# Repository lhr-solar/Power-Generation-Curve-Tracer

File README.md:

# :sunny: PV Curve Tracer

- [:sunny: PV Curve Tracer](#sunny-pv-curve-tracer)
  - [Repository Structure](#repository-structure)
  - [Maintainers and Contribution](#maintainers-and-contribution)
  - [Versioning](#versioning)
  - [TODO](#todo)

---

## Repository Structure

- **datasheets** - contains datasheets for major components of the PV Curve Tracer.
- **docs** - contains documentation on how to build, test, and use the PV Curve Tracer.
- **fw** - contains fw that is loaded onto the PV Curve Tracer.
  - **tests** - test programs used to characterize and validate the PV Curve Tracer.
  - **src** - main program used to run the PV Curve Tracer.
  - **inc** - internally developed libraries specific for the PV Curve Tracer.
  - **lib** - third party libraries used by the PV Curve Tracer.
- **hw**
  - **Footprints** - project specfic footprint association files for the PV Curve Tracer.
  - **Models** - 3d .step files for the PCB 3d viewer.
  - **Symbols** - project specific symbol files for the PV Curve Tracer.
  - **vX_Y_Z** - frozen versioning folder for PCB production files.

---

## Maintainers and Contribution

The current maintainer of this project is Matthew Yu as of 05/20/2023. His email
is [matthewjkyu@gmail.com](matthewjkyu@gmail.com).

Contributors to the HW and FW encompass many dedicated students, including:

- Roy Mor
- Afnan Mir
- Youssef Elsherif

Special thanks to Professor Gary Hallock, who supervised the development and
design of this project.

---

## Versioning

This PCB is on unified version `1.3.0`. Every time the schematic and/or layout
is updated, this version number should go up. We use [semantic
versioning](https://semver.org/) to denote between versions. See the
[changelog](./docs/CHANGELOG.md) for more details.

---

## TODO

Documentation

- Update assembly and testing document, ordering document, and improvement document.
- Add datasheets for key components of the device.

HW

- check if v1.2.0 bodges has been fixed (op amps, regulator)
   Complete v1.4.0rc board candidate

SW

- Regenerate code for MBED with proposed filestructure

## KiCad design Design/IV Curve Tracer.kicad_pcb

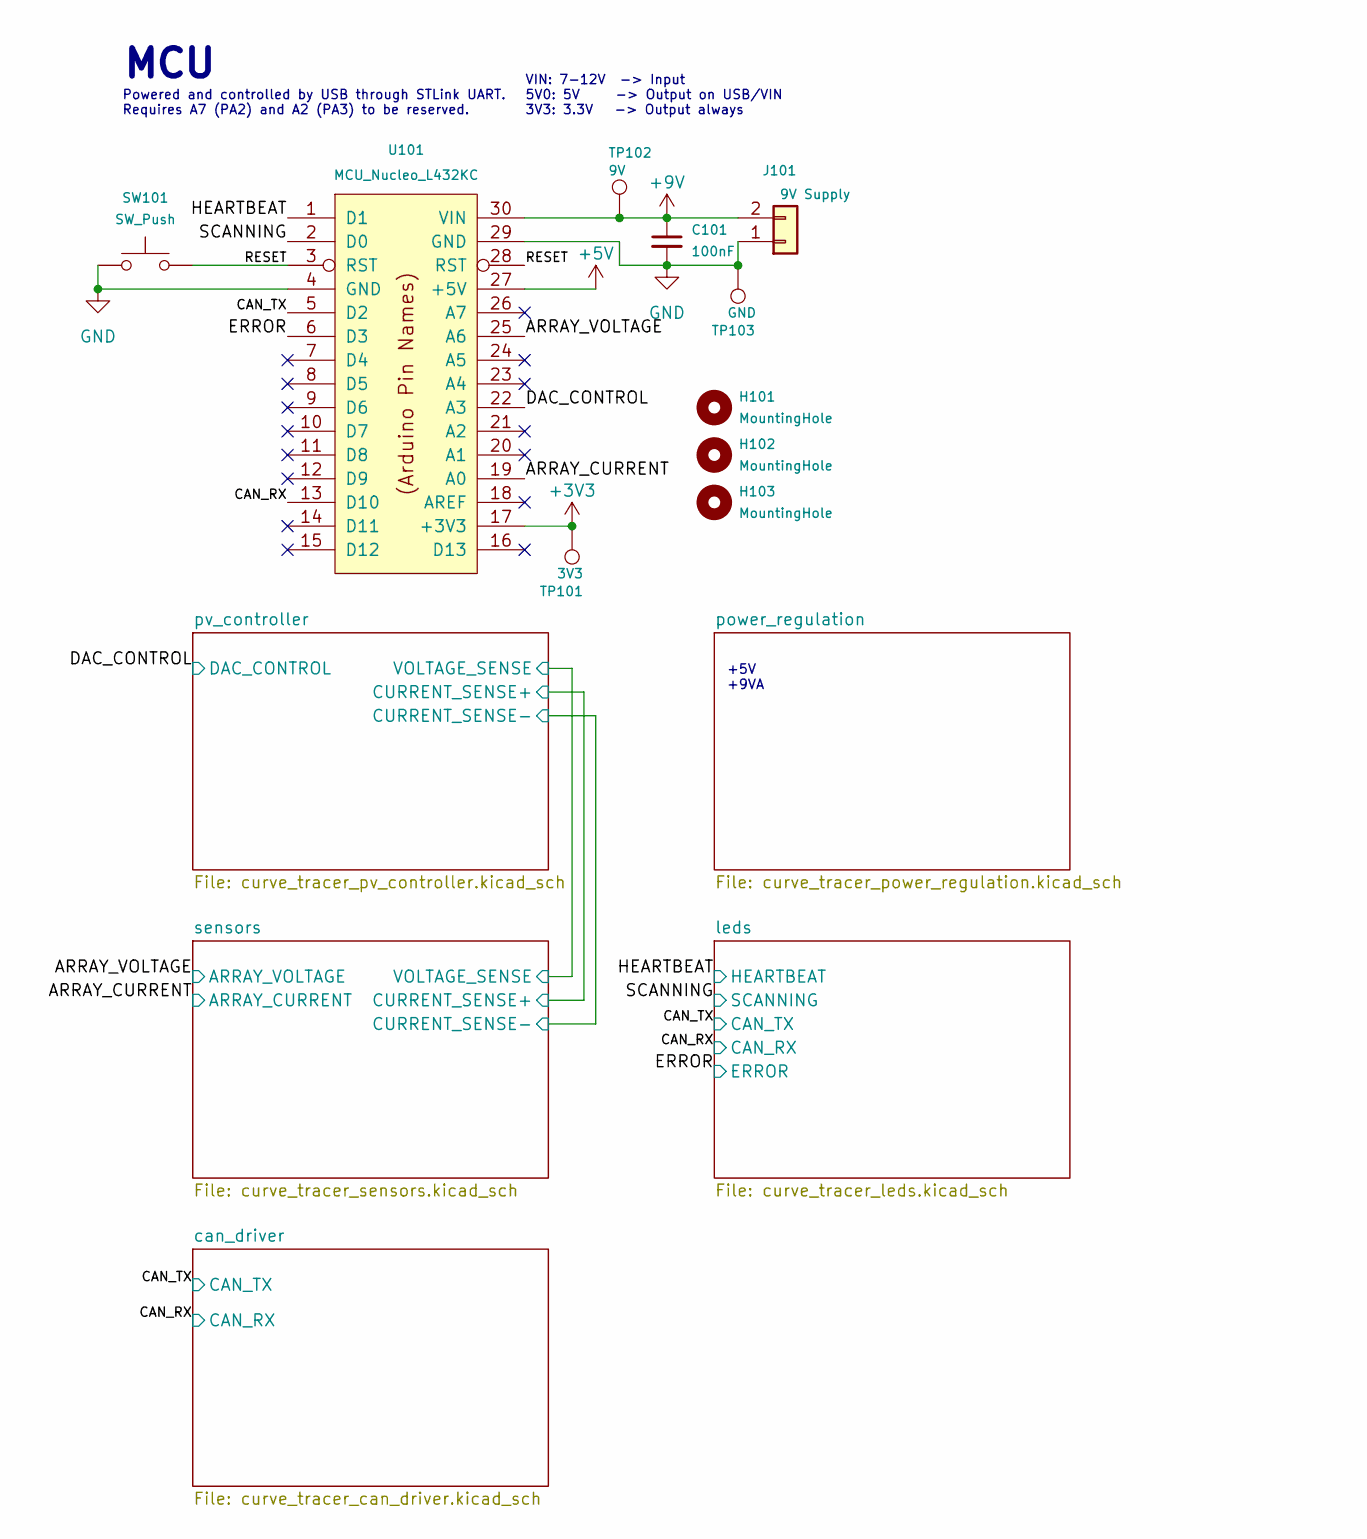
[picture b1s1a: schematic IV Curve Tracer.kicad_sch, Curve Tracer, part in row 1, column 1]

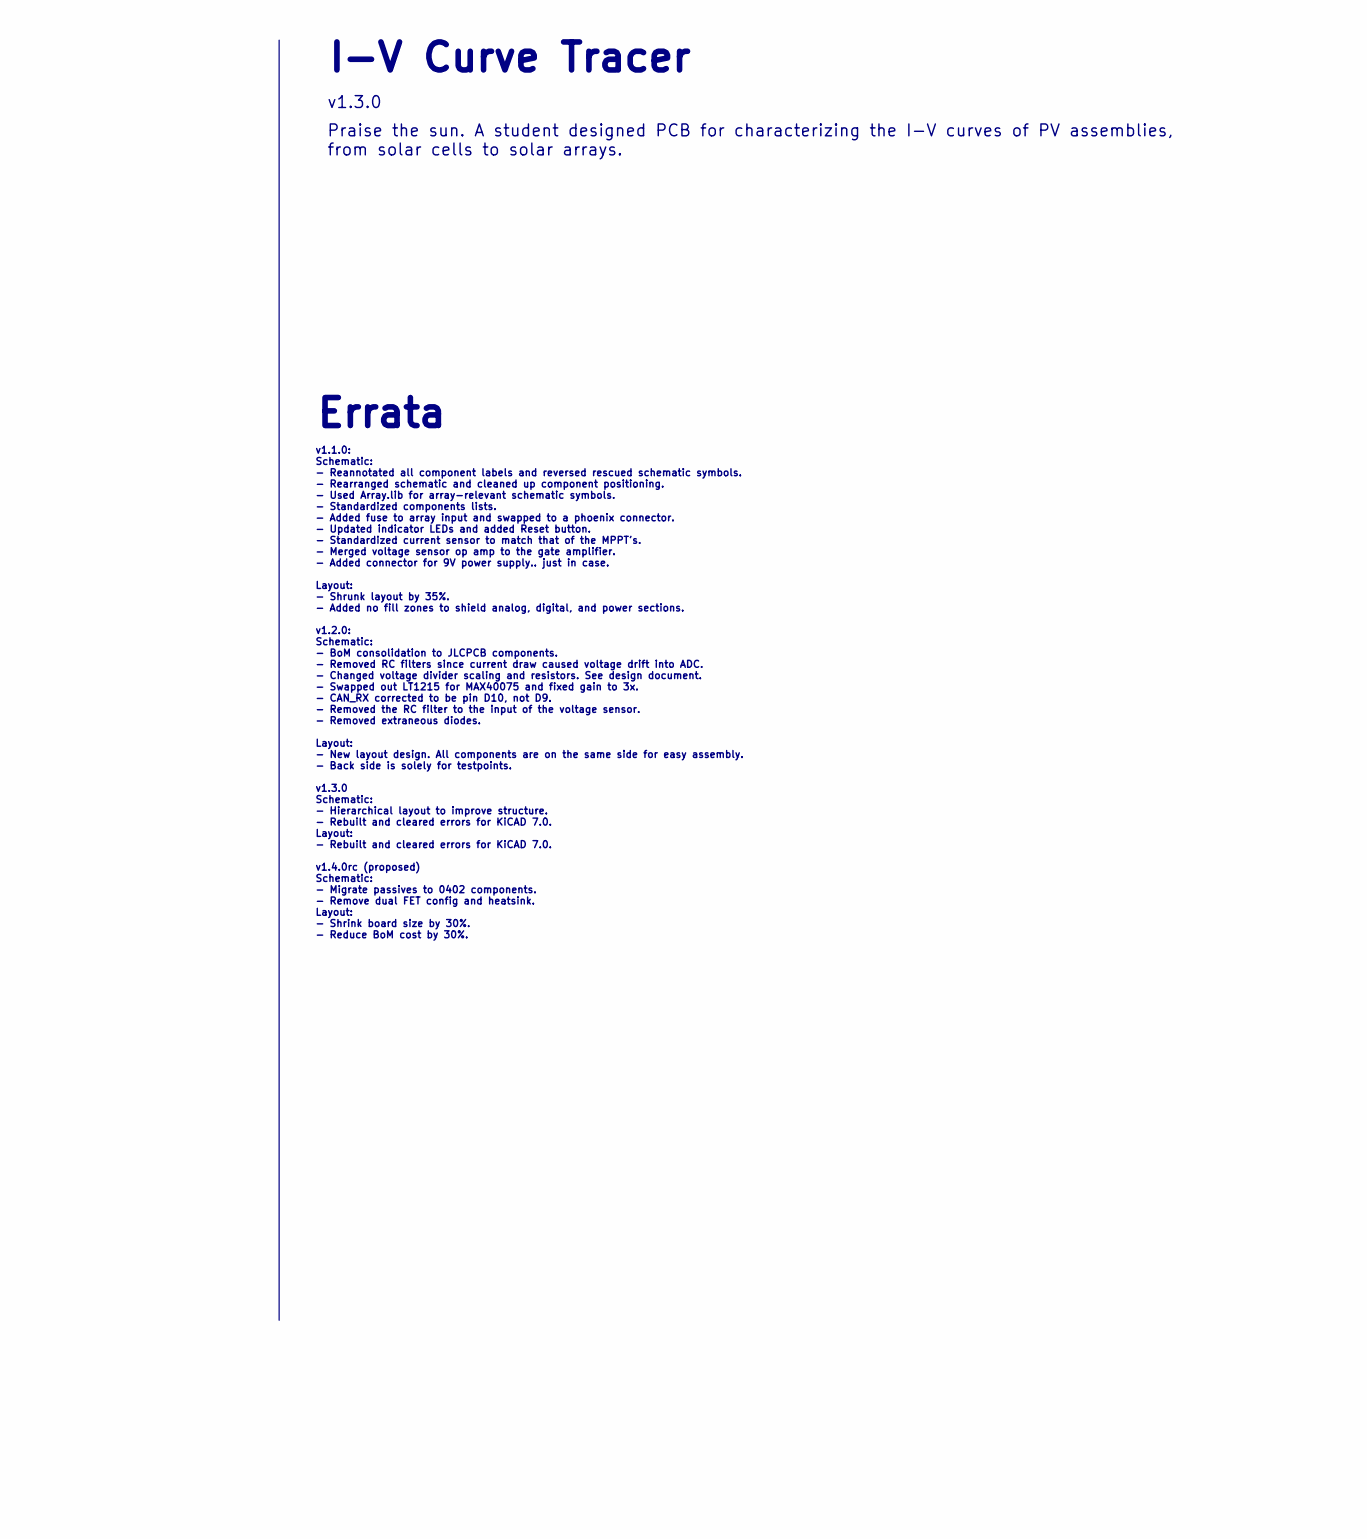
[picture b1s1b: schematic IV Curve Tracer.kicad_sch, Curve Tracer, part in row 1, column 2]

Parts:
C101: 100nF; C_0805_2012Metric; LCSC Part # C28233
H101, H102, H103: MountingHole; MountingHole_2.2mm_M2
J101: 9V Supply; Molex_Micro-Fit_3.0_43650-0215_1x02_P3.00mm_Vertical
SW101: SW_Push; SW_PUSH_6mm
TP101: 3V3; TestPoint_Pad_1.0x1.0mm
TP102: 9V; TestPoint_Pad_1.0x1.0mm
TP103: GND; TestPoint_Pad_1.0x1.0mm
U101: MCU_Nucleo_L432KC; MODULE_NUCLEO-L432KC

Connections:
+3V3: TP101.1, U101.17 (+3V3); also elsewhere on the board
+5V: U101.27 (+5V); also elsewhere on the board
+9V: C101.1, J101.2, TP102.1, U101.30 (VIN)
/ARRAY_CURRENT: U101.19 (A0); also elsewhere on the board
/ARRAY_VOLTAGE: U101.25 (A6); also elsewhere on the board
/CAN_RX: U101.13 (D10); also elsewhere on the board
/CAN_TX: U101.5 (D2); also elsewhere on the board
/DAC_CONTROL: U101.22 (A3); also elsewhere on the board
/ERROR: U101.6 (D3); also elsewhere on the board
/HEARTBEAT: U101.1 (D1); also elsewhere on the board
/RESET: SW101.2, U101.3 (RST), U101.28 (RST)
/SCANNING: U101.2 (D0); also elsewhere on the board
GND: C101.2, J101.1, SW101.1, TP103.1, U101.4 (GND), U101.29 (GND); also elsewhere on the board

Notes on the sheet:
Errata
Praise the sun. A student designed PCB for characterizing the I-V curves of PV assemblies, from solar cells to solar arrays.
I-V Curve Tracer
+5V +9VA
MCU
Powered and controlled by USB through STLink UART. Requires A7 (PA2) and A2 (PA3) to be reserved.
v1.1.0: Schematic: - Reannotated all component labels and reversed rescued schematic symbols. - Rearranged schematic and cleaned up component positioning. - Used Array.lib for array-relevant schematic symbols. - Standardized components lists. - Added fuse to array input and swapped to a phoenix con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
v1.3.0
VIN: 7-12V -> Input 5V0: 5V -> Output on USB/VIN 3V3: 3.3V -> Output always

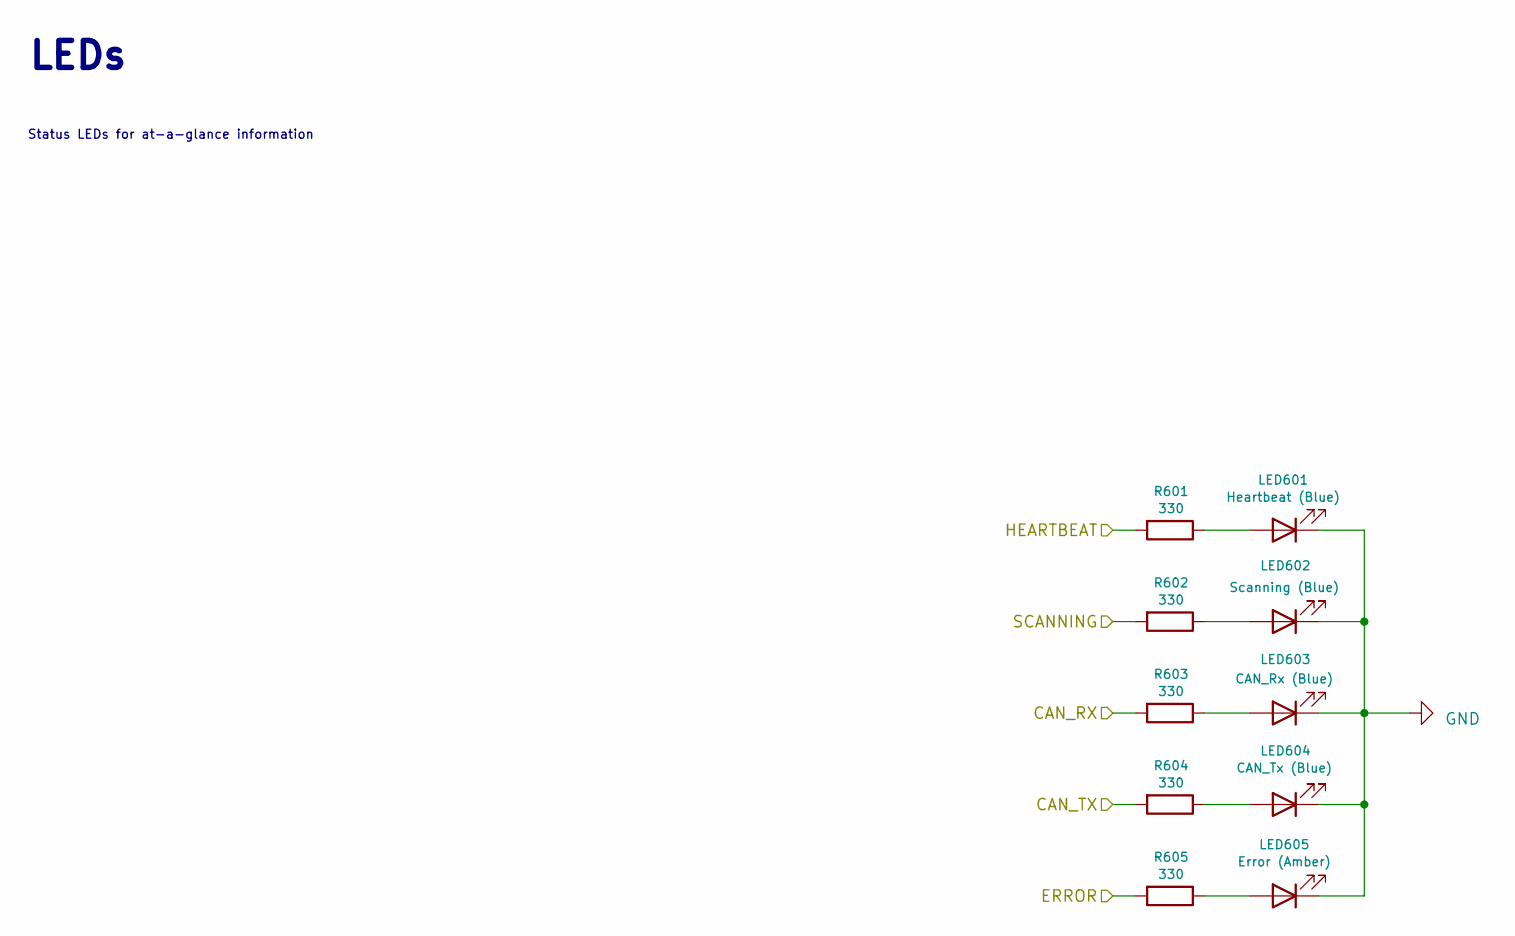
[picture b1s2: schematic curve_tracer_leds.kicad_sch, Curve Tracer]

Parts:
LED601: Heartbeat (Blue); LED_0805_2012Metric
LED602: Scanning (Blue); LED_0805_2012Metric
LED603: CAN_Rx (Blue); LED_0805_2012Metric
LED604: CAN_Tx (Blue); LED_0805_2012Metric
LED605: Error (Amber); LED_0805_2012Metric
R601, R602, R603, R604, R605: 330; R_0805_2012Metric; LCSC Part # C17630

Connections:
/CAN_RX: R603.2; also elsewhere on the board
/CAN_TX: R604.2; also elsewhere on the board
/ERROR: R605.2; also elsewhere on the board
/HEARTBEAT: R601.2; also elsewhere on the board
/SCANNING: R602.2; also elsewhere on the board
GND: LED601.1 (K), LED602.1 (K), LED603.1 (K), LED604.1 (K), LED605.1 (K); also elsewhere on the board
unnamed: LED601.2 (A), R601.1
unnamed: LED602.2 (A), R602.1
unnamed: LED603.2 (A), R603.1
unnamed: LED604.2 (A), R604.1
unnamed: LED605.2 (A), R605.1

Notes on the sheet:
Status LEDs for at-a-glance information
LEDs

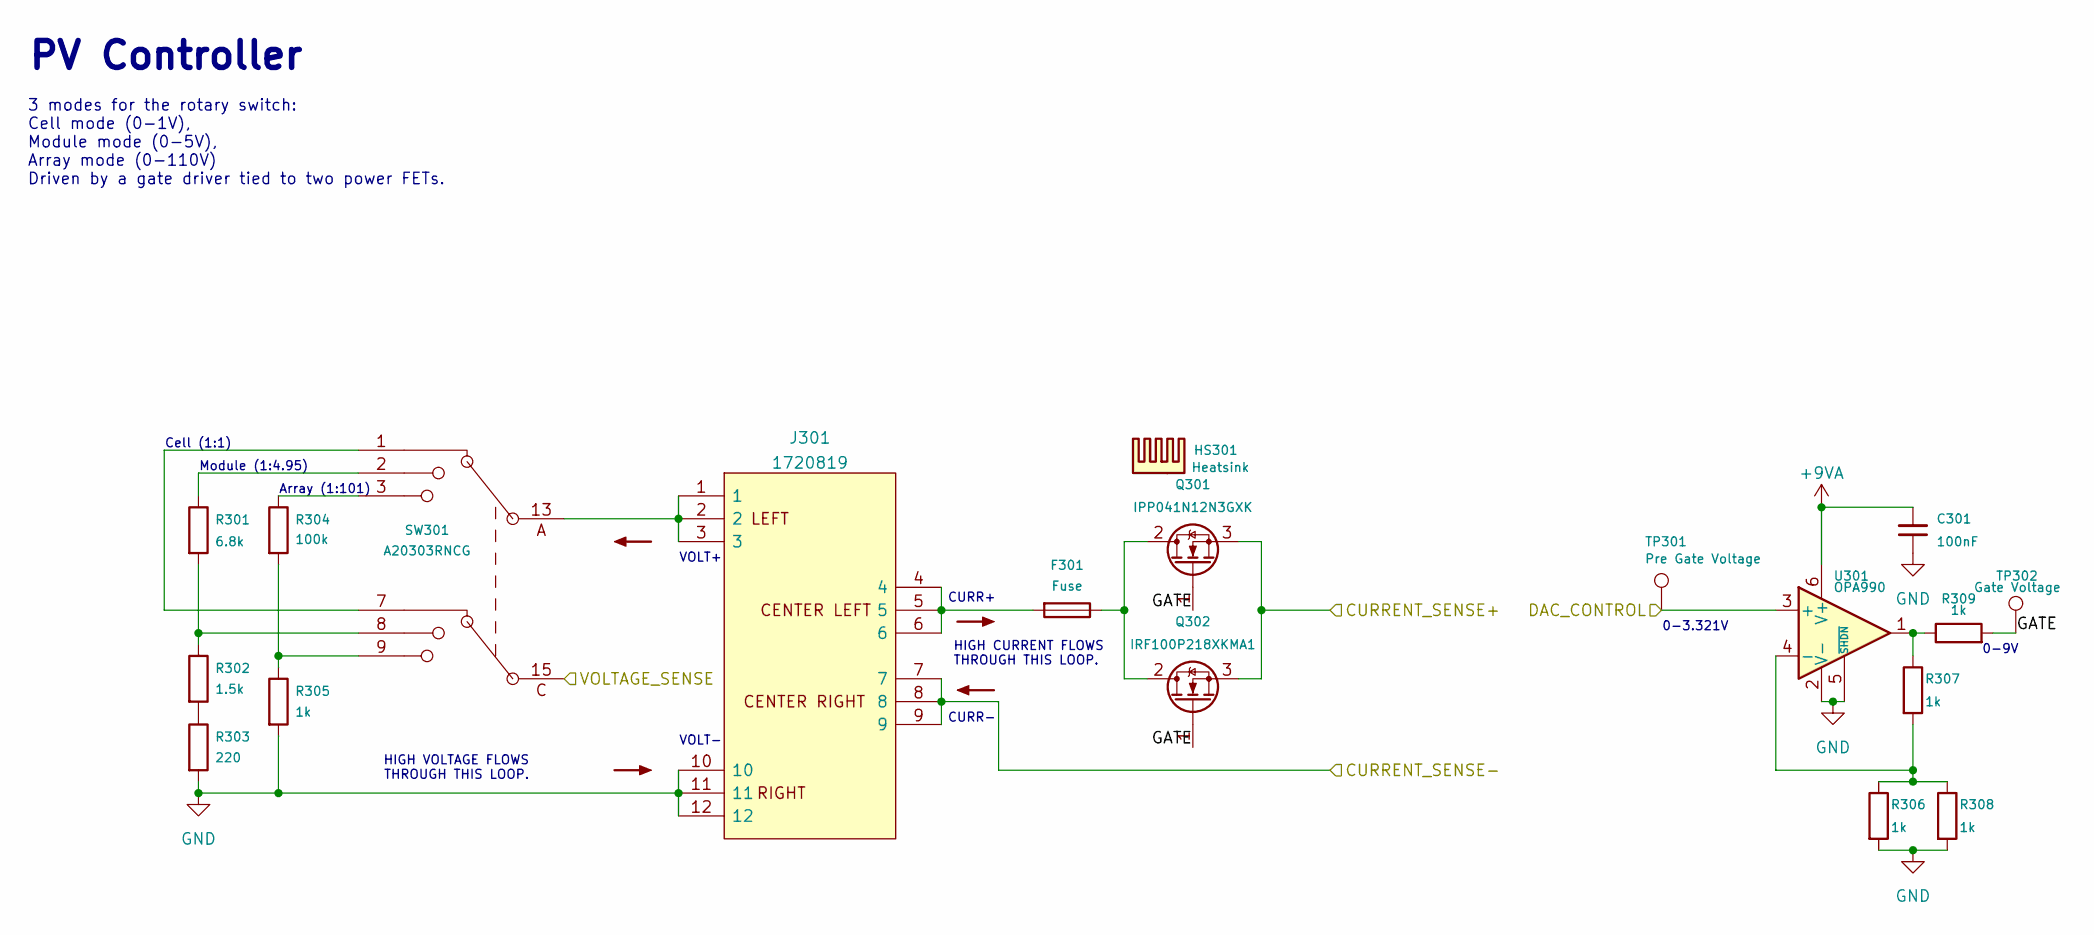
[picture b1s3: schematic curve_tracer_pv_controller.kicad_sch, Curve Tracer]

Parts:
C301: 100nF; C_0805_2012Metric; LCSC Part # C28233
F301: Fuse; 05200101Z_Fuze_Holder_5x20_PCB_Mount
HS301: Heatsink; Heatsink_Fischer_SK129-STS_42x25mm_2xDrill2.5mm
J301: 1720819
Q301: IPP041N12N3GXK; TO-220-3_Vertical
Q302: IRF100P218XKMA1; TO-220-3_Vertical
R301: 6.8k; R_0805_2012Metric; LCSC Part # C17772
R302: 1.5k; R_0805_2012Metric; LCSC Part # C4310
R303: 220; R_0805_2012Metric; LCSC Part # C17557
R304: 100k; R_0805_2012Metric; LCSC Part # C149504
R305, R306, R307, R308, R309: 1k; R_0805_2012Metric; LCSC Part # C17513
SW301: A20303RNCG; A20303RNCG_rotary_sw_dp3t
TP301: Pre Gate Voltage; TestPoint_Pad_1.0x1.0mm
TP302: Gate Voltage; TestPoint_Pad_1.0x1.0mm
U301: OPA990; SOT-23-6

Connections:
+9VA: C301.2, U301.6 (V+); also elsewhere on the board
/DAC_CONTROL: TP301.1, U301.3 (+); also elsewhere on the board
/pv_controller/CURRENT_SENSE+: Q301.3 (S), Q302.3 (S); also elsewhere on the board
/pv_controller/CURRENT_SENSE-: J301.7, J301.8, J301.9; also elsewhere on the board
/pv_controller/GATE: Q301.1 (G), Q302.1 (G), R309.2, TP302.1
/pv_controller/VOLTAGE_SENSE: SW301.15 (C); also elsewhere on the board
GND: C301.1, J301.10, J301.11, J301.12, R303.2, R305.2, R306.2, R308.2, U301.2 (V-), U301.5 (~SHDN); also elsewhere on the board
unnamed: F301.2, J301.4, J301.5, J301.6
unnamed: F301.1, Q301.2 (D), Q302.2 (D)
unnamed: R301.1, SW301.2
unnamed: R301.2, R302.1, SW301.8
unnamed: R302.2, R303.1
unnamed: R304.1, SW301.3
unnamed: R304.2, R305.1, SW301.9
unnamed: R307.1, R309.1, U301.1
unnamed: J301.1, J301.2, J301.3, SW301.13 (A)
unnamed: SW301.1, SW301.7
unnamed: R306.1, R307.2, R308.1, U301.4 (-)

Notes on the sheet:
PV Controller
VOLT+
0-3.321V
HIGH CURRENT FLOWS THROUGH THIS LOOP.
3 modes for the rotary switch: Cell mode (0-1V), Module mode (0-5V), Array mode (0-110V) Driven by a gate driver tied to two power FETs.
CURR+
Module (1:4.95)
0-9V
CURR-
HIGH VOLTAGE FLOWS THROUGH THIS LOOP.
Cell (1:1)
Array (1:101)
VOLT-

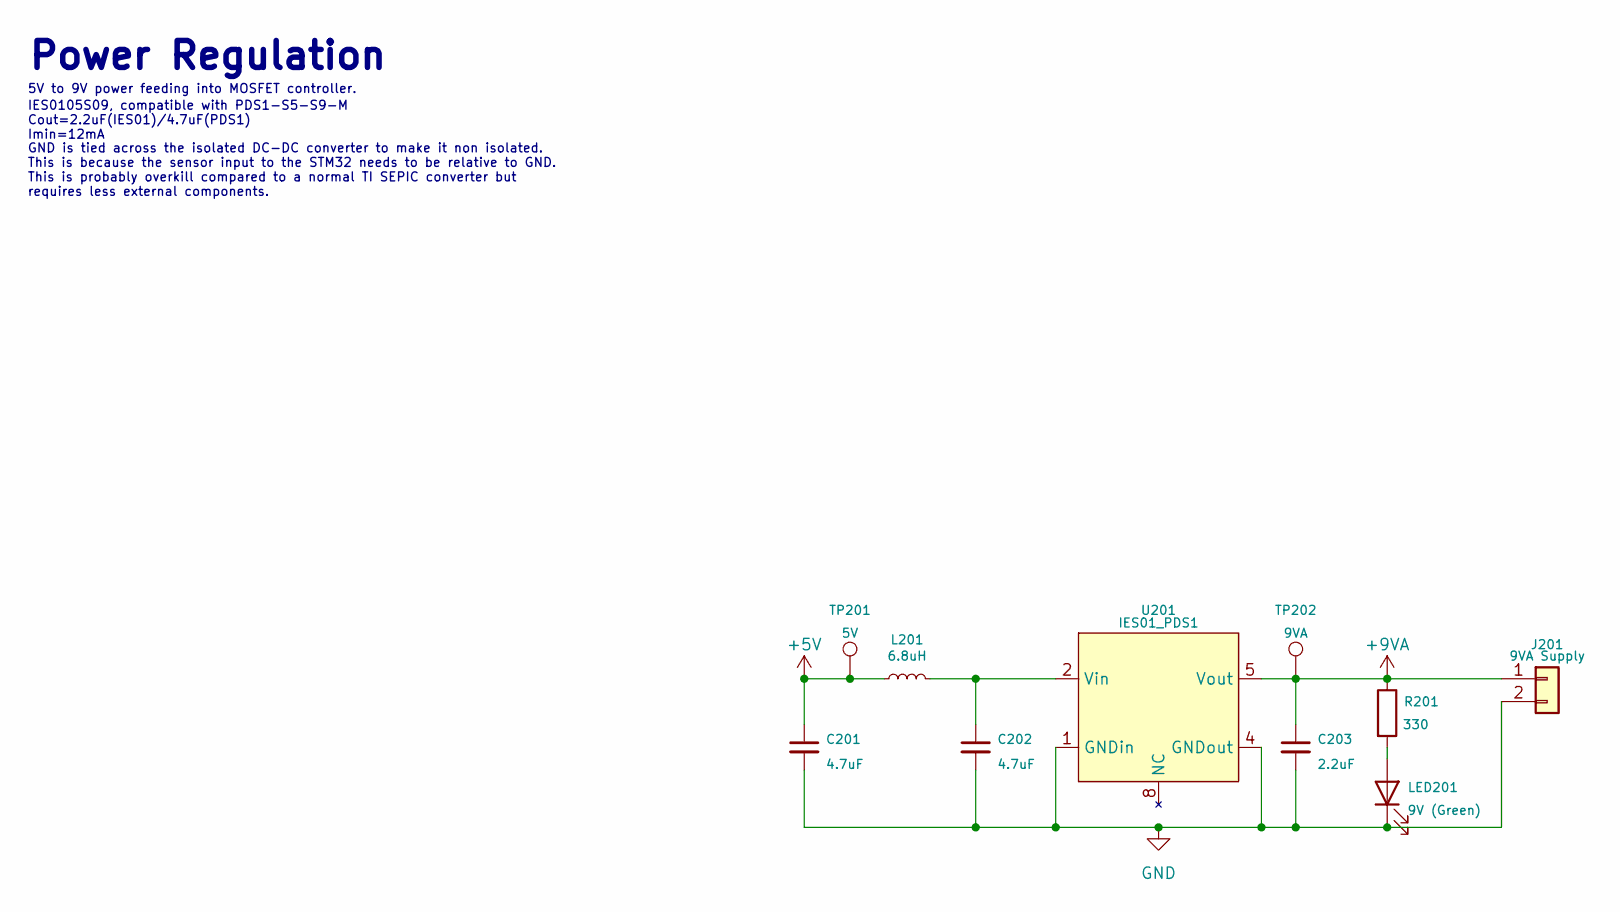
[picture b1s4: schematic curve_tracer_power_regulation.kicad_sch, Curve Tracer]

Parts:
C201, C202: 4.7uF; C_0805_2012Metric; LCSC Part # C1779
C203: 2.2uF; C_0805_2012Metric; LCSC Part # C49217
J201: 9VA Supply; Molex_Micro-Fit_3.0_43650-0215_1x02_P3.00mm_Vertical
L201: 6.8uH; L_Taiyo-Yuden_NR-50xx
LED201: 9V (Green); LED_0805_2012Metric
R201: 330; R_0805_2012Metric; LCSC Part # C17630
TP201: 5V; TestPoint_Pad_1.0x1.0mm
TP202: 9VA; TestPoint_Pad_1.0x1.0mm
U201: IES01_PDS1

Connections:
+5V: C201.1, L201.1, TP201.1; also elsewhere on the board
+9VA: C203.1, J201.1, R201.1, TP202.1, U201.5 (Vout); also elsewhere on the board
GND: C201.2, C202.2, C203.2, J201.2, LED201.1 (K), U201.1 (GNDin), U201.4 (GNDout); also elsewhere on the board
unnamed: LED201.2 (A), R201.2
unnamed: C202.1, L201.2, U201.2 (Vin)

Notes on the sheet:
GND is tied across the isolated DC-DC converter to make it non isolated. This is because the sensor input to the STM32 needs to be relative to GND. This is probably overkill compared to a normal TI SEPIC converter but requires less external components.
IES0105S09, compatible with PDS1-S5-S9-M Cout=2.2uF(IES01)/4.7uF(PDS1) Imin=12mA
Power Regulation
5V to 9V power feeding into MOSFET controller.

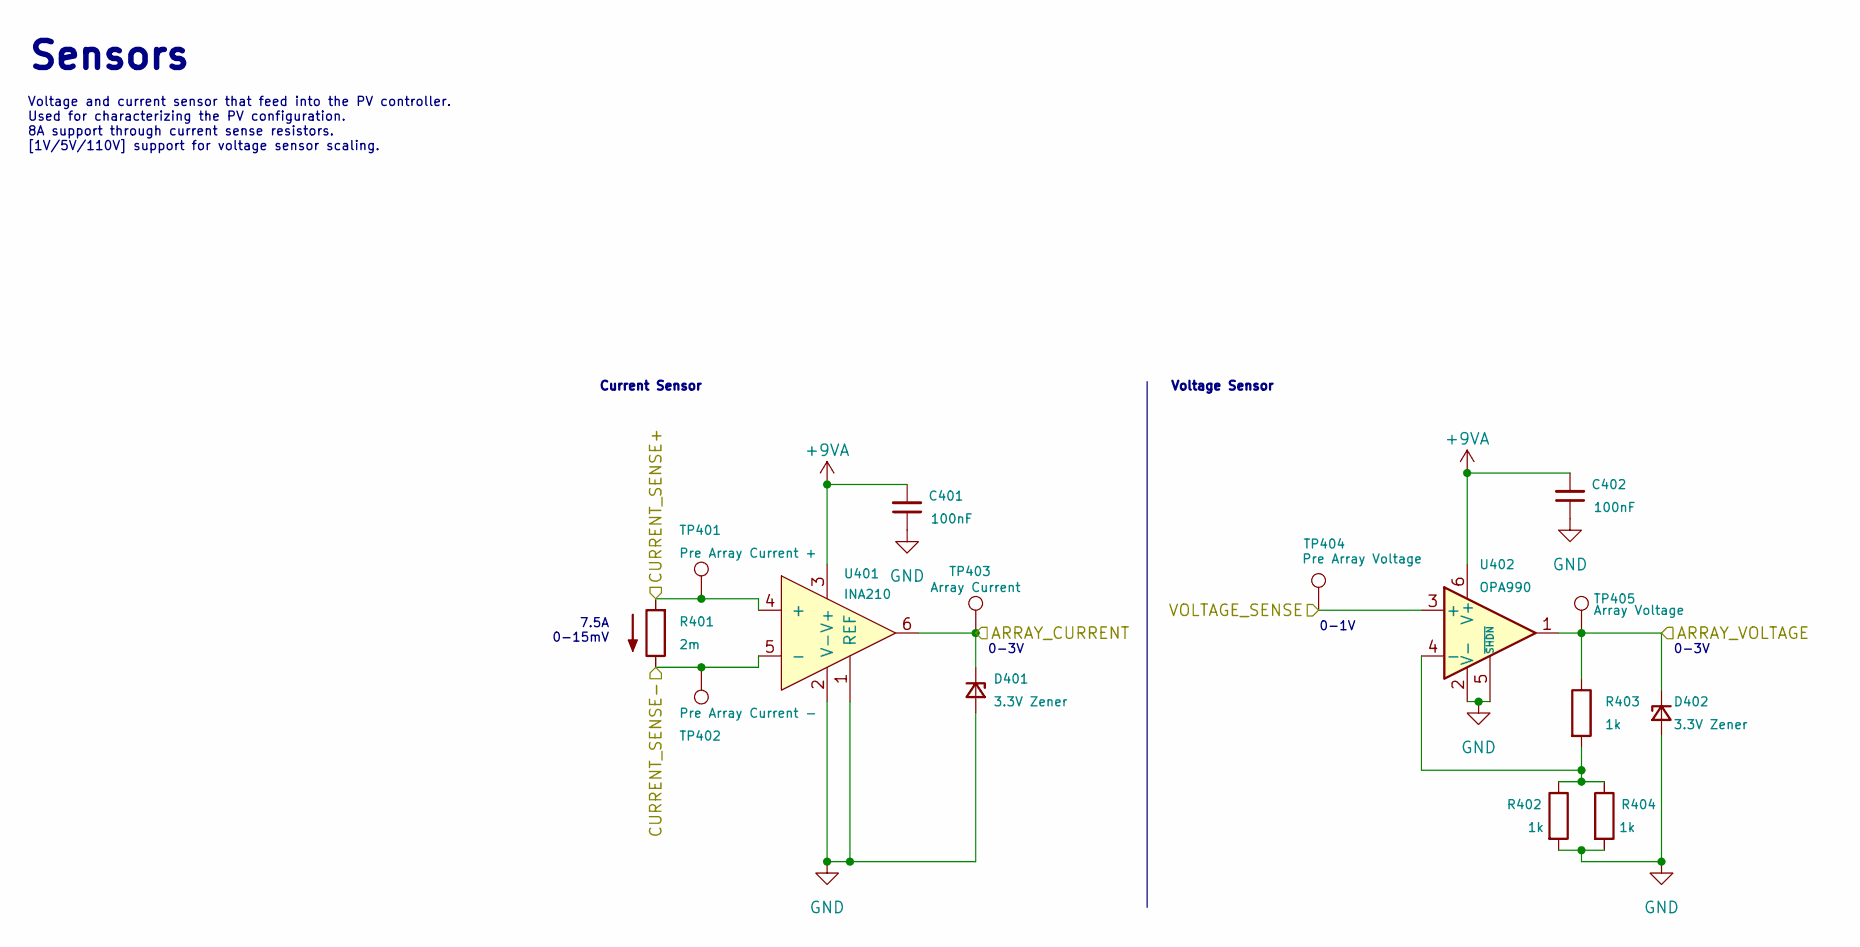
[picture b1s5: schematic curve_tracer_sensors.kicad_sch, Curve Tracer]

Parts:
C401, C402: 100nF; C_0805_2012Metric; LCSC Part # C28233
D401, D402: 3.3V Zener; D_MiniMELF; LCSC Part # C8056
R401: 2m; R_1206_3216Metric
R402, R403, R404: 1k; R_0805_2012Metric; LCSC Part # C17513
TP401: Pre Array Current +; TestPoint_Pad_1.0x1.0mm
TP402: Pre Array Current -; TestPoint_Pad_1.0x1.0mm
TP403: Array Current; TestPoint_Pad_1.0x1.0mm
TP404: Pre Array Voltage; TestPoint_Pad_1.0x1.0mm
TP405: Array Voltage; TestPoint_Pad_1.0x1.0mm
U401: INA210; SOT-363_SC-70-6_Handsoldering
U402: OPA990; SOT-23-6

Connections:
+9VA: C401.2, C402.2, U401.3 (V+), U402.6 (V+); also elsewhere on the board
/ARRAY_CURRENT: D401.1 (K), TP403.1, U401.6; also elsewhere on the board
/ARRAY_VOLTAGE: D402.1 (K), R403.1, TP405.1, U402.1; also elsewhere on the board
/pv_controller/CURRENT_SENSE+: R401.2, TP401.1, U401.4 (+); also elsewhere on the board
/pv_controller/CURRENT_SENSE-: R401.1, TP402.1, U401.5 (-); also elsewhere on the board
/pv_controller/VOLTAGE_SENSE: TP404.1, U402.3 (+); also elsewhere on the board
GND: C401.1, C402.1, D401.2 (A), D402.2 (A), R402.2, R404.2, U401.1 (REF), U401.2 (V-), U402.2 (V-), U402.5 (~SHDN); also elsewhere on the board
unnamed: R402.1, R403.2, R404.1, U402.4 (-)

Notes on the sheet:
0-3V
Sensors
Voltage and current sensor that feed into the PV controller. Used for characterizing the PV configuration. 8A support through current sense resistors. [1V/5V/110V] support for voltage sensor scaling.
Voltage Sensor
0-1V
7.5A 0-15mV
Current Sensor

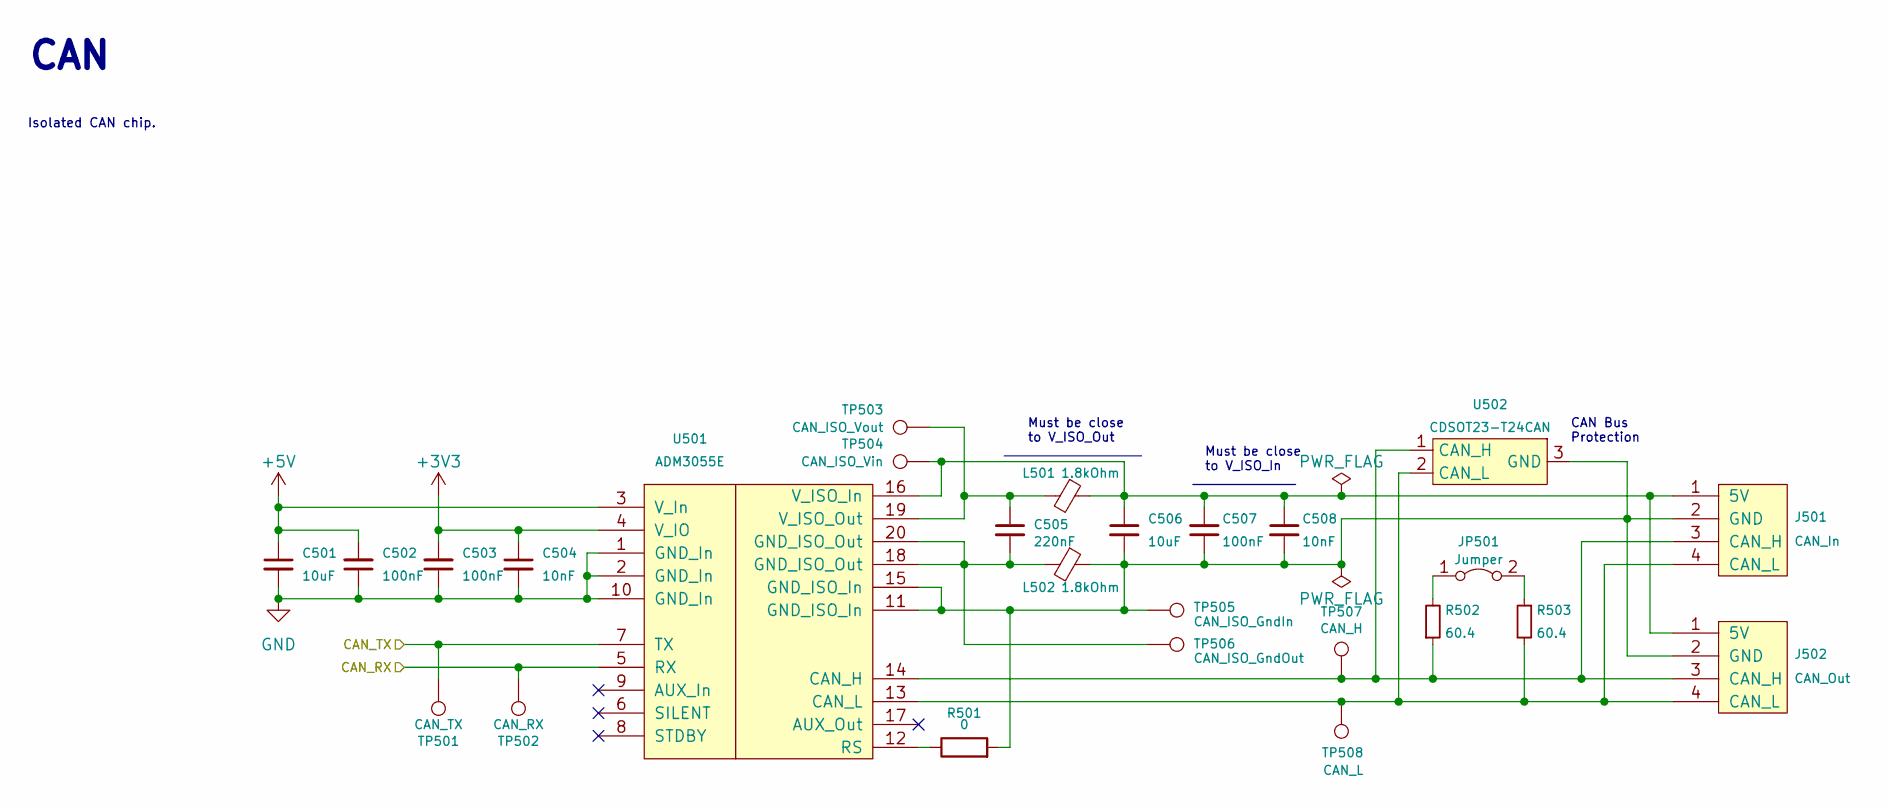
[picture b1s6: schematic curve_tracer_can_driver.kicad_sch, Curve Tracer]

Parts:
C501, C506: 10uF; C_0805_2012Metric; LCSC Part # C15850
C502, C503, C507: 100nF; C_0805_2012Metric; LCSC Part # C28233
C504, C508: 10nF; C_0805_2012Metric; LCSC Part # C1710
C505: 220nF; C_0805_2012Metric; LCSC Part # C5378
J501: CAN_In; Molex_Micro-Fit_3.0_43650-0415_1x04_P3.00mm_Vertical
J502: CAN_Out; Molex_Micro-Fit_3.0_43650-0415_1x04_P3.00mm_Vertical
JP501: Jumper; PinHeader_1x02_P2.54mm_Vertical
L501, L502: 1.8kOhm; L_0805_2012Metric
R501: 0; R_0805_2012Metric; LCSC Part # C17477
R502, R503: 60.4; R_0805_2012Metric
TP501: CAN_TX; TestPoint_Pad_1.0x1.0mm
TP502: CAN_RX; TestPoint_Pad_1.0x1.0mm
TP503: CAN_ISO_Vout; TestPoint_Pad_1.0x1.0mm
TP504: CAN_ISO_Vin; TestPoint_Pad_1.0x1.0mm
TP505: CAN_ISO_GndIn; TestPoint_Pad_1.0x1.0mm
TP506: CAN_ISO_GndOut; TestPoint_Pad_1.0x1.0mm
TP507: CAN_H; TestPoint_Pad_1.0x1.0mm
TP508: CAN_L; TestPoint_Pad_1.0x1.0mm
U501: ADM3055E; ADM3055EBRIZ
U502: CDSOT23-T24CAN; SOT-23

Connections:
+3V3: C503.2, C504.1, U501.4 (V_IO); also elsewhere on the board
+5V: C501.1, C502.2, U501.3 (V_In); also elsewhere on the board
/CAN_RX: TP502.1, U501.5 (RX); also elsewhere on the board
/CAN_TX: TP501.1, U501.7 (TX); also elsewhere on the board
GND: C501.2, C502.1, C503.1, C504.2, U501.1 (GND_In), U501.2 (GND_In), U501.10 (GND_In); also elsewhere on the board
unnamed: C505.2, L502.2, TP506.1, U501.18 (GND_ISO_Out), U501.20 (GND_ISO_Out)
unnamed: C506.1, C507.2, C508.1, J501.1 (5V), J502.1 (5V), L501.1, TP504.1, U501.16 (V_ISO_In)
unnamed: J501.3 (CAN_H), J502.3 (CAN_H), R502.1, TP507.1, U501.14 (CAN_H), U502.1 (CAN_H)
unnamed: J501.4 (CAN_L), J502.4 (CAN_L), R503.2, TP508.1, U501.13 (CAN_L), U502.2 (CAN_L)
unnamed: C506.2, C507.1, C508.2, J501.2 (GND), J502.2 (GND), L502.1, R501.2, TP505.1, U501.11 (GND_ISO_In), U501.15 (GND_ISO_In), U502.3 (GND)
unnamed: JP501.1 (A), R502.2
unnamed: JP501.2 (B), R503.1
unnamed: R501.1, U501.12 (RS)
unnamed: C505.1, L501.2, TP503.1, U501.19 (V_ISO_Out)

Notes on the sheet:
CAN Bus Protection
CAN
Must be close to V_ISO_Out
Isolated CAN chip.
Must be close to V_ISO_In

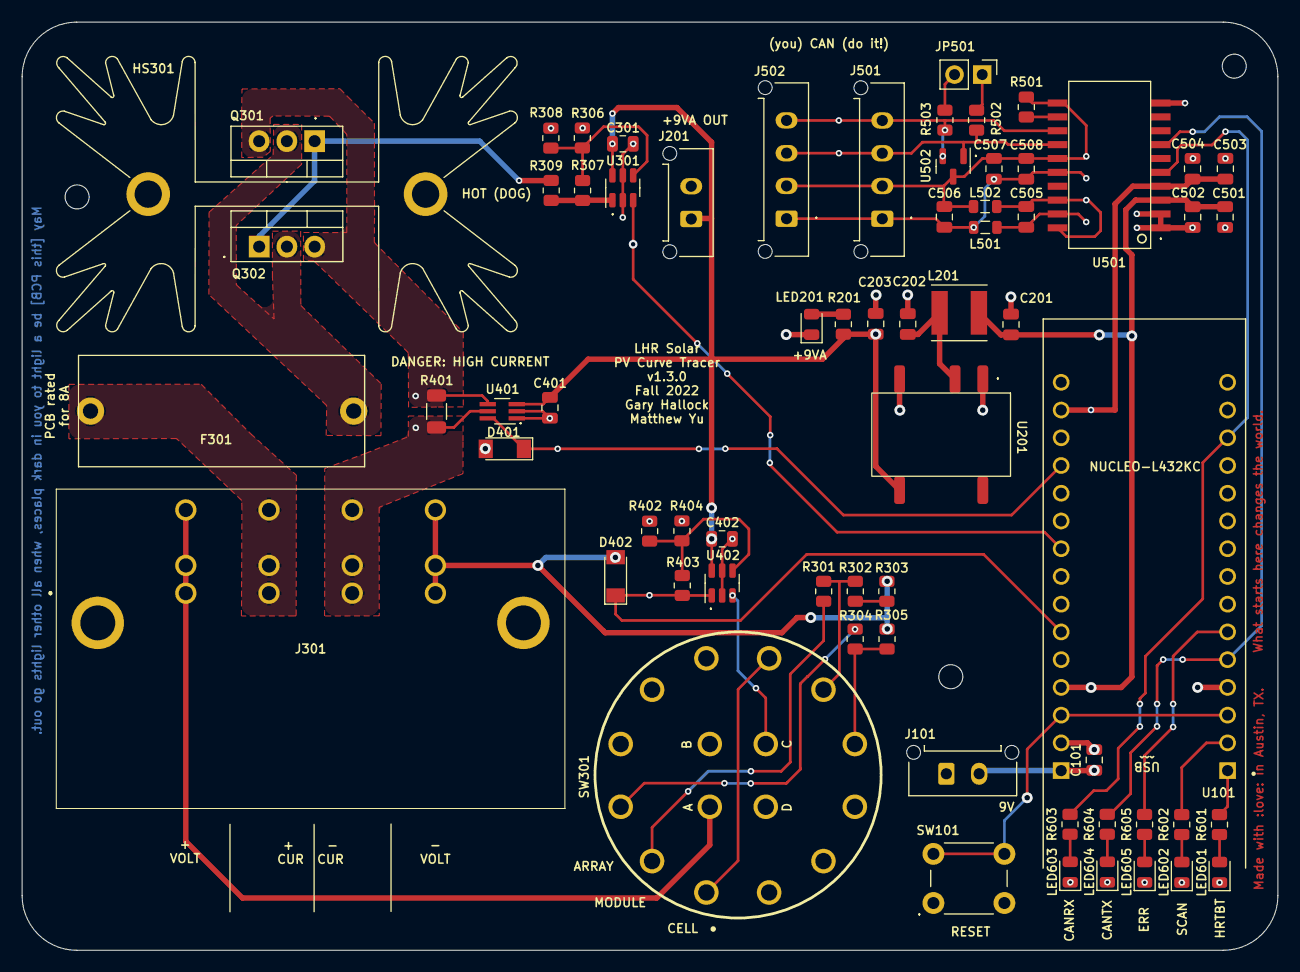
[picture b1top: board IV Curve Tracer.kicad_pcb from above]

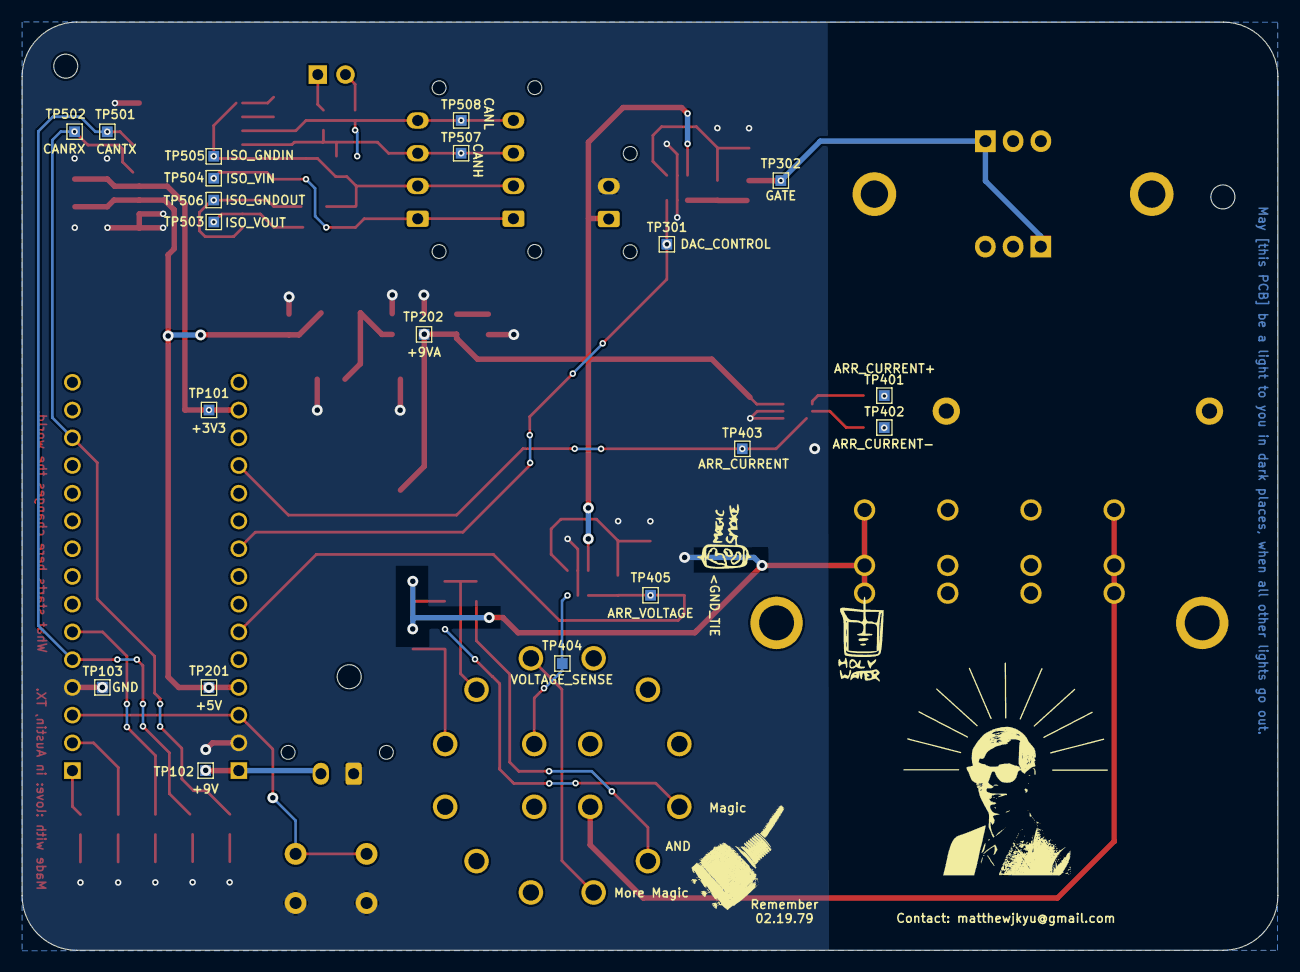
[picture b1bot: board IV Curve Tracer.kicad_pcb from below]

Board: 4 copper layers, 115.0 x 85.0 mm, 90 parts (20 on the bottom side), 46 nets.

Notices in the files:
parts and their libraries:
Copyright 2016 Accelerated Designs. All rights reserved.
